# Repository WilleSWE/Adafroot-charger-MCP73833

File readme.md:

# MCP73833 Li-Po/Li-Ion Charger (REV 1B)

A highly flexible Li-Po and Li-Ion battery charger built around the Microchip **MCP73833** IC. 

This board features a selectable charging current via a 2x5 pin header, allowing you to quickly switch between preset currents using a standard 2.54mm jumper shunt. It also includes two configurable THT slots for any custom current limit under 1000mA.

## Key Features
- **USB-C Powered:** Input via a 6-pin USB-C plug (USB4125-GF).
- **Universal Battery Output:** Features JST-PH (2.0mm), JST-ZH (1.5mm), and PicoBlade (1.25mm) connectors to fit almost any hobby battery.
- **Dedicated LED Indicators:** Clear status lights for **Power Good (PG)**, **STAT1 (Charging)**, and **STAT2 (Complete)**.
- **Built-in Storage:** A handy 1x2 header to store your jumper pin when not in use.
- **On-Board Cheat Sheet:** A complete LED status truth table silkscreened directly onto the back of the PCB.

## Charging Current Calculation
The charging current is set by the though-hole resistors R4 R8 R9 R10 R11.
Formula is also available to google, but:
Charging current (mA) = 1000 / Rprog (KΩ)
For example, 10 KΩ resistor gives charging speed of 100mA. 
Meanwhile 20KΩ is 50mA
And, 1 KΩ would be the physical limit of the charging IC ( 1 Amp ), so don't go lower than 1 kohm! *(Or you will let out the magic smoke, and you can only do that **once**)*

### Default Jumper Configurations:
- **50mA:** 20 kΩ resistor
- **100mA:** 10 kΩ resistor
- **213mA:** 4.7 kΩ resistor
- **1000mA:** 1 kΩ resistor
- **Spare 2 aka R11:** Open THT slot for any custom current under 1000mA (Minimum 1 kΩ).

## Bill of Materials (BOM)

### SMD Components (0603 & IC)
- **1x** MCP73833-FCI/UN (MSOP-10 package)
- **2x** 10 µF Ceramic Capacitors (0603)
- **2x** 5.1 kΩ Resistors (0603) – *For USB-C CC pins, so not exactly required but recommended*
- **3x** LEDs (0603) – *Red for PG, Blue for STAT1, Green for STAT2 is what i used*
- **3x** ~330 Ω Resistors (0603) – *Current limiting for LEDs*

### Connectors & THT Components
- **1x** USB-C Receptacle (GCT USB4125-GF or compatible 6-pin)
- **3x** JST 2-pin Battery Connectors (1.25mm, 1.5mm, 2.0mm pitch.) (Although, remember to only plug in one battery at a time! The plugs are connected together so differently charged batteries would try to even out without a limit on the current. Or cause a fire)
- **1x** 2x5 (or 2x 1x5) Female Pin Header (2.54mm pitch)
- **1x** 1x2 Female Pin Header (2.54mm pitch) – *Jumper storage*
- **1x** 2.54mm Jumper
- **Up to 6x** THT Axial Resistors (Choose values based on desired mA, minimum 2 required for basic operation (NTC and one charging Speed)

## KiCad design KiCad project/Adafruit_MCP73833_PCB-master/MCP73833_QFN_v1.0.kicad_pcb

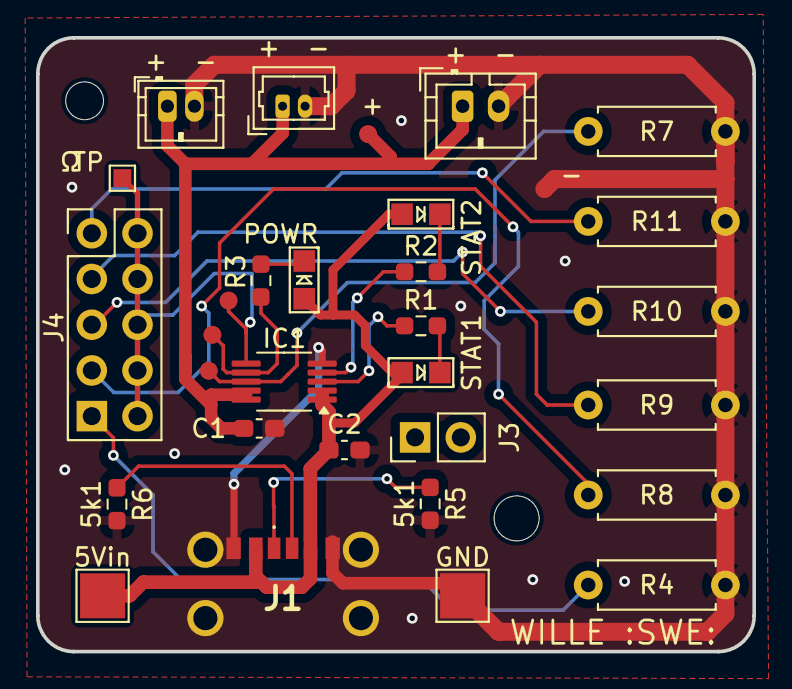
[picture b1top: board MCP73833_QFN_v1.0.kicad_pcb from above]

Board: 2 copper layers, 39.8 x 34.1 mm, 26 parts (0 on the bottom side), 18 nets.

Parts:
5Vin: 5Vin; TestPoint_Pad_2.5x2.5mm
+  -: JST-PH 2.0mm; JST_PH_B2B-PH-K_1x02_P2.00mm_Vertical
+  -#2: PicoBlade 1.25mm; Molex_PicoBlade_53047-0210_1x02_P1.25mm_Vertical
+  -#3: JST-ZH 1.5mm; JST_ZH_B2B-ZR_1x02_P1.50mm_Vertical
C1, C2: 10uF; C_0603_1608Metric_Pad1.08x0.95mm_HandSolder
GND: Gnd; TestPoint_Pad_2.5x2.5mm
IC1: MCP73833-FCI_UN; MSOP-10_3x3mm_P0.5mm
J1: USB_C_Receptacle_PowerOnly_6P; USB4125GFA0190
J3: Conn_01x02; PinHeader_1x02_P2.54mm_Vertical
J4: Conn_02x05_Counter_Clockwise; PinHeader_2x05_P2.54mm_Vertical
LED1: STAT1-ORANGE; CHIPLED_0805
LED2: STAT2-GREEN; CHIPLED_0805
LED3: Power-RED; CHIPLED_0805
R1, R2, R3: 680 ohm 0603; R_0603_1608Metric_Pad0.98x0.95mm_HandSolder
R4: 10k ohm; R_Axial_DIN0207_L6.3mm_D2.5mm_P7.62mm_Horizontal
R5, R6: 5k1; R_0603_1608Metric_Pad0.98x0.95mm_HandSolder
R7: 10K/THERM; R_Axial_DIN0207_L6.3mm_D2.5mm_P7.62mm_Horizontal
R8: 4.7k ohm; R_Axial_DIN0207_L6.3mm_D2.5mm_P7.62mm_Horizontal
R9: SPARE; R_Axial_DIN0207_L6.3mm_D2.5mm_P7.62mm_Horizontal
R10: 1k ohm; R_Axial_DIN0207_L6.3mm_D2.5mm_P7.62mm_Horizontal
R11: SPARE 2; R_Axial_DIN0207_L6.3mm_D2.5mm_P7.62mm_Horizontal
TP: TestPoint_Pad_1.0x1.0mm

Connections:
5.0V: 5Vin.1, C2.1, IC1.1 (VDD_1), IC1.2 (VDD_2), J1.A9 (VBUS), J1.B9 (VBUS), LED1.A, LED2.A, LED3.A
GND: + -.2, + -#2.2, + -#3.2, C1.2, C2.2, GND.1, IC1.5 (VSS), J1.A12 (GND), J1.B12 (GND), J1.MH1, J1.MH2, J1.MH3, J1.MH4, R4.1, R5.2, R6.2, R7.1, R8.1, R9.1, R10.1, R11.1
unnamed: + -.1, + -#2.1, + -#3.1, C1.1, IC1.9 (VBAT_1), IC1.10 (VBAT_2)
unnamed: IC1.6 (PROG), J4.6, J4.7, J4.8, J4.9, J4.10, TP.1
unnamed: IC1.3 (STAT1), R1.1
unnamed: IC1.4 (STAT2), R2.1
unnamed: IC1.8 (THERM), R7.2
unnamed: IC1.7 (~PG), R3.2
unnamed: J1.A5 (CC1), R5.1
unnamed: J1.B5 (CC2), R6.1
unnamed: J4.1, R4.2
unnamed: J4.2, R8.2
unnamed: J4.3, R10.2
unnamed: J4.4, R9.2
unnamed: J4.5, R11.2
unnamed: LED1.C, R1.2
unnamed: LED2.C, R2.2
unnamed: LED3.C, R3.1

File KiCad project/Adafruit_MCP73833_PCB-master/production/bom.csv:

Designator,Footprint,Quantity,Value,LCSC Part #
+  -_3,JST_PH_B2B-PH-K_1x02_P2.00mm_Vertical,1,JST-PH 2.0mm,
+  -_2,Molex_PicoBlade_53047-0210_1x02_P1.25mm_Vertical,1,PicoBlade 1.25mm,
+  -,JST_ZH_B2B-ZR_1x02_P1.50mm_Vertical,1,JST-ZH 1.5mm,
5VIN,TestPoint_Pad_2.5x2.5mm,1,5Vin,
"C1, C2",0603,2,10uF,
GND,TestPoint_Pad_2.5x2.5mm,1,Gnd,
IC1,MSOP-10_3x3mm_P0.5mm,1,MCP73833-FCI_UN,
J1,USB4125GFA0190,1,USB_C_Receptacle_PowerOnly_6P,
J3,PinHeader_1x02_P2.54mm_Vertical,1,Conn_01x02,
J4,PinHeader_2x05_P2.54mm_Vertical,1,Conn_02x05_Counter_Clockwise,
LED1,CHIPLED_0805,1,STAT1-ORANGE,
LED2,CHIPLED_0805,1,STAT2-GREEN,
LED3,CHIPLED_0805,1,Power-RED,
"R1, R2, R3",0603,3,680 ohm 0603,
R10,R_Axial_DIN0207_L6.3mm_D2.5mm_P7.62mm_Horizontal,1,1k ohm,
R11,R_Axial_DIN0207_L6.3mm_D2.5mm_P7.62mm_Horizontal,1,SPARE 2,
R4,R_Axial_DIN0207_L6.3mm_D2.5mm_P7.62mm_Horizontal,1,10k ohm,
"R5, R6",0603,2,5k1,
R7,R_Axial_DIN0207_L6.3mm_D2.5mm_P7.62mm_Horizontal,1,10K/THERM,
R8,R_Axial_DIN0207_L6.3mm_D2.5mm_P7.62mm_Horizontal,1,4.7k ohm,
R9,R_Axial_DIN0207_L6.3mm_D2.5mm_P7.62mm_Horizontal,1,SPARE,
